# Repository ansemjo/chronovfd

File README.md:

# chronovfd

A vacuum-flourescent display (VFD) clock project based on Soviet NOS [IVL2-7/5 / ИВЛ2-7/5](https://www.ebay.com/sch/i.html?_nkw=ivl2-7%2F5) tubes. This has been my first somewhat complex hardware project when I got into electronics design in 2020 and grew to multiple iterations over the years.

#### quickmenu:

* [vfddriver](vfddriver/) — updated display board, which can be used over I2C
* [sandwich](sandwich/) — the original clock design with two boards
* [other](#other-directories) — links to initial research prototypes and various experiments

### vfddriver

This section describes the updated display board design, which I will be using going forward with this project. The [original design](#sandwich) of course still works but I found it needlessly complex later on due to a few choices I made.

Primarily, you needed to have a lot of IVL2-7/5 specific bits in the firmware and constantly refresh the display contents on the shift register. The mapping of display characters to segment anodes, their mapping to the correct shift-register pin, as well as the necessary anode and grid time-multiplexing all needed to be implemented on the controller board. Which meant that you really couldn't easily swap out the controller for something else. It had originally been a design goal not to require *any* separate firmware on the display board but I realized that just makes everything more complicated because you can't handle the display as an abstraction.

Instead, in this redesign I opted to include a small AVR ATtiny414 microcontroller, simplify the filament AC driver circuit with an H-bridge and implement the entire board as an I2C peripheral. **That newer design, along with firmware and documentation, can be found in [`vfddriver/`](vfddriver/).**

In these images above you can also see why there is no dedicated "clockdriver v2" yet: now that the VFD is controlled over I2C, you can just use a small CircuitPython board with a Qwiic cable, like the [Adafruit QT Py ESP32-S3](https://www.adafruit.com/product/5426). :)

### sandwich

What you see in the pictures below is the original "sandwich design" with a pure-logic display driver (more or less a wrapper around the HV5812 shift-register) and an ESP32-based design with an RTC and coin-cell backup for the controller board. You can find all the KiCAD files and firmware for it in [`sandwich/`](sandwich/), together with the original README and more photos.

### other directories

The **[research/](research/) directory** contains a lot of initial ideas and fundamental information on VFD operation (needed voltages etc.) along with the [display datasheets](research/ivl2-7_5-datasheets).

The first **prototype clock** on perfboard can be found in [research/protoclock/](research/protoclock/).

An alternative **LCD-based front panel** with compatible dimensions, which can also be used standalone in [lcddriver](lcddriver/).

In [experiments/si4706_radio_eval](experiments/si4706_radio_eval/) there is an evaluation board based on the **Skyworks Si4706 FM receiver** with RDS decoding. The idea is that you should be able to get time signal from radio stations without any need for internet synchronization.

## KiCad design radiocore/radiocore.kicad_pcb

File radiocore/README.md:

# radiocore
This is a redesign of the [`si4706_radio_eval`](../experiments/si4706_radio_eval/) experiment, meant to be a "clockcore v2" to control the standalone vfddriver.

Notably, it includes:

* **Skyworks Si4706** FM radio receiver with RDS decoder, to get time signal "from the air"
* **DS1338 RTC** with coin cell battery backup, to keep accurate time over long periods and without power
* **ESP32-C3** as a simple-to-program-over-USB controller chip, which conveniently *also* includes WiFi capability, if you prefer NTP over RDS
* vertical **GCT USB4145** USB-C connector, so a final assembly with two sandwiched boards will have the cable coming in from the back

_**2026-02-03:** I ordered the boards and am waiting to try if the CircuitPython firmware from the experiment will work on this chip as well. (**edit:** yes, it does!)_

### errata

While the overall function works (reception is even better than expected, to be honest), I also made a few major mistakes:

* The Neopixel is supplied with VBUS (~ 5V) but only gets logic level 3.3V on its data pin from the ESP32. When the VBUS supply voltage is slightly over 5V (like 5.2–5.3V), the Neopixel consistenly stays dark. When it is exactly at or slightly under 5V, you can *sometimes* get it to work. At 5V, the SK6812 requires a 3.6V logic level per the datasheet. Oops.

* The UPDI connection (pin 5 on the side header) is connected directly to the ESP32 without level shifting or current limit. Since this pin is at 5V logic level on the ATtiny, you could damage the ESP32-C3 if it is ever connected during programming of the `vfddriver`. Use a Qwiic cable only or just solder the first four pins to be safe.

* While it works out, the cutout under the Qwiic connector is a little close to properly insert the plug while the cable is already weaved through the hole.

* In the previous `vfddriver` firmware, the display's address was `0x68` and thus collided with the RTC. I've moved the VFD to address `0x42` and you can still reconfigure it using the `user_row`, of course.

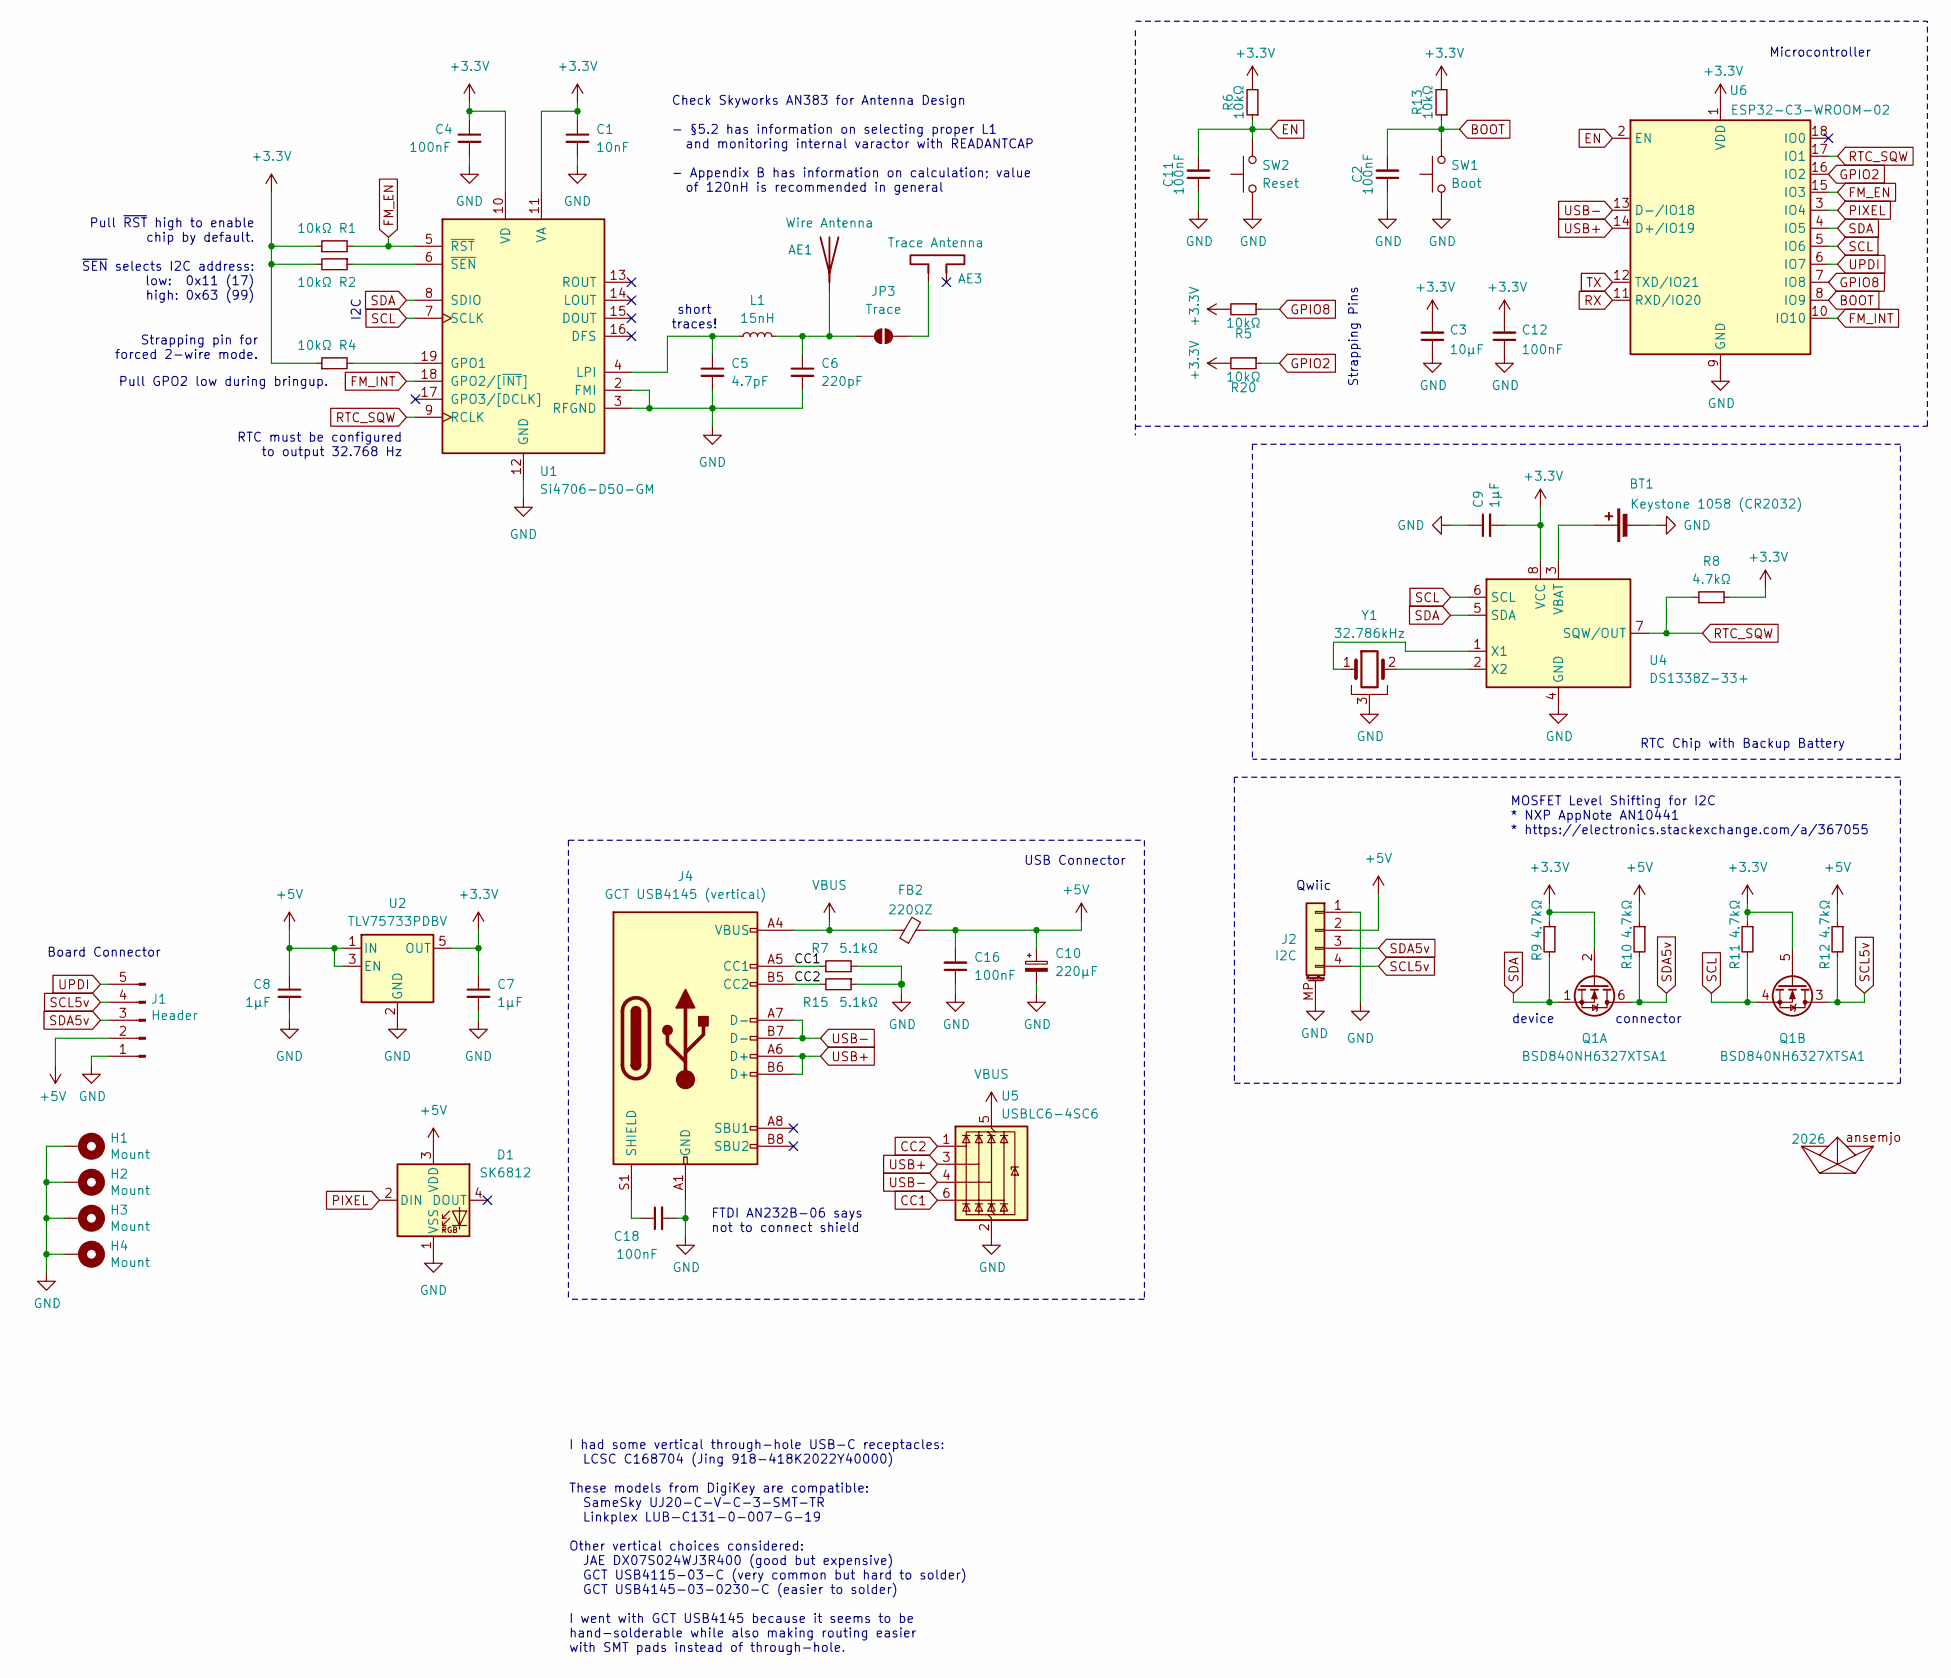
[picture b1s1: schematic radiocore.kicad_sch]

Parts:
A1: 2026; ahoi
AE1: Wire Antenna; TestPoint_THTPad_D2.0mm_Drill1.0mm
AE3: Trace Antenna
BT1: Keystone 1058 (CR2032); BatteryHolder_Keystone_1058_1x2032; MPN 1058; Digi-Key_PN 36-1058-ND
C1: 10nF; C_0805_2012Metric_Pad1.18x1.45mm_HandSolder
C2, C4, C11, C12, C16: 100nF; C_0805_2012Metric_Pad1.18x1.45mm_HandSolder
C3: 10µF; C_0805_2012Metric_Pad1.18x1.45mm_HandSolder
C5: 4.7pF; C_0805_2012Metric_Pad1.18x1.45mm_HandSolder
C6: 220pF; C_0805_2012Metric_Pad1.18x1.45mm_HandSolder
C7, C8: 1µF; C_0805_2012Metric_Pad1.18x1.45mm_HandSolder
C9: 1µF; C_0805_2012Metric_Pad1.18x1.45mm_HandSolder; MPN CL21B105KAFNNNG; Digi-Key_PN 1276-6469-1-ND
C10: 220µF; CP_EIA-3528-12_Kemet-T_HandSolder
C18: 100nF; C_0805_2012Metric_Pad1.18x1.45mm_HandSolder; MPN CL21B104KACNNNC; Digi-Key_PN 1276-1099-1-ND
D1: SK6812; LED_SK6812_PLCC4_5.0x5.0mm_P3.2mm
FB2: 220ΩZ; L_0805_2012Metric_Pad1.05x1.20mm_HandSolder
H1, H2, H3, H4: Mount; MountingHole_2.7mm_M2.5_Pad
J1: Header; PinHeader_1x05_P2.54mm_Vertical; MPN PREC040DBAN-M71RC; Digi-Key PN S2112EC-40-ND
J2: I2C; JST_SH_SM04B-SRSS-TB_1x04-1MP_P1.00mm_Horizontal
J4: GCT USB4145 (vertical); GCT_USB4145-03-0230-C_REVA2
JP3: Trace; SolderJumper-2_P1.3mm_Open_RoundedPad1.0x1.5mm
L1: 15nH; L_0805_2012Metric_Pad1.05x1.20mm_HandSolder
Q1: BSD840NH6327XTSA1; SOT-363_SC-70-6
R1, R2, R4, R5, R6, R13, R20: 10kΩ; R_0805_2012Metric_Pad1.20x1.40mm_HandSolder
R7, R15: 5.1kΩ; R_0805_2012Metric_Pad1.20x1.40mm_HandSolder
R8: 4.7kΩ; R_0805_2012Metric_Pad1.20x1.40mm_HandSolder; MPN RC0805FR-074K7L; Digi-Key_PN 311-4.70KCRCT-ND
R9, R10, R11, R12: 4.7kΩ; R_0805_2012Metric_Pad1.20x1.40mm_HandSolder
SW1: Boot; SW_SPST_PTS810
SW2: Reset; SW_SPST_PTS810
U1: Si4706-D50-GM; SiliconLabs_QFN-20-1EP_3x3mm_P0.5mm_EP1.8x1.8mm
U2: TLV75733PDBV; SOT-23-5
U4: DS1338Z-33+; SOIC-8_3.9x4.9mm_P1.27mm; MPN DS1338Z-33+T&R; Digi-Key_PN DS1338Z-33+T&RCT-ND
U5: USBLC6-4SC6; SOT-23-6; MPN USBLC6-4SC6; Digi-Key_PN 497-4492-1-ND
U6: ESP32-C3-WROOM-02; ESP-WROOM-02
Y1: 32.786kHz; Crystal_SMD_MicroCrystal_MS1V-T1K

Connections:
+3.3V: C1.1, C3.2, C4.1, C7.1, C9.2, C12.2, Q1.2 (G), Q1.5 (G), R1.1, R2.2, R4.1, R5.2, R6.2, R8.2, R9.1, R11.1, R13.2, R20.2, U1.10 (VD), U1.11 (VA), U2.5 (OUT), U4.8 (VCC), U6.1 (VDD)
+5V: C8.1, C10.1, C16.2, D1.3 (VDD), FB2.2, J1.2, J2.2, R10.1, R12.1, U2.1 (IN), U2.3 (EN)
BOOT: C2.2, R13.1, SW1.2, U6.8 (IO9)
CC1: J4.A5 (CC1), R7.1, U5.6 (I/O4)
CC2: J4.B5 (CC2), R15.2, U5.1 (I/O1)
EN: C11.2, R6.1, SW2.2, U6.2 (EN)
FM_EN: R1.2, U1.5 (~RST), U6.15 (IO3)
FM_INT: U1.18 (GPO2/[~INT]), U6.10 (IO10)
GND: BT1.2 (-), C1.2, C2.1, C3.1, C4.2, C5.2, C6.2, C7.2, C8.2, C9.1, C10.2, C11.1, C12.1, C16.1, C18.2, D1.1 (VSS), H1.1, H2.1, H3.1, H4.1, J1.1, J2.1, J2.MP (MountPin), J4.A1 (GND), J4.A12 (GND), J4.B1 (GND), J4.B12 (GND), R7.2, R15.1, SW1.1, SW2.1, U1.2 (FMI), U1.3 (RFGND), U1.12 (GND), U1.21 (GND), U2.2 (GND), U4.4 (GND), U5.2 (GND), U6.9 (GND), U6.19 (GND), Y1.3
GPIO2: R20.1, U6.16 (IO2)
GPIO8: R5.1, U6.7 (IO8)
unnamed: AE1.1 (A), C6.1, JP3.1 (A), L1.2
unnamed: BT1.1 (+), U4.3 (VBAT)
unnamed: C18.1, J4.S1 (SHIELD)
unnamed: AE3.1, JP3.2 (B)
unnamed: R4.2, U1.19 (GPO1)
unnamed: C5.1, L1.1, U1.4 (LPI)
unnamed: R2.1, U1.6 (~SEN)
unnamed: U4.1 (X1), Y1.1
unnamed: U4.2 (X2), Y1.2
PIXEL: D1.2 (DIN), U6.3 (IO4)
RTC_SQW: R8.1, U1.9 (RCLK), U4.7 (SQW/OUT), U6.17 (IO1)
RX: U6.11 (RXD/IO20)
SCL: Q1.4 (S), R11.2, U1.7 (SCLK), U4.6 (SCL), U6.5 (IO6)
SCL5v: J1.4, J2.4, Q1.3 (D), R12.2
SDA: Q1.1 (S), R9.2, U1.8 (SDIO), U4.5 (SDA), U6.4 (IO5)
SDA5v: J1.3, J2.3, Q1.6 (D), R10.2
TX: U6.12 (TXD/IO21)
UPDI: J1.5, U6.6 (IO7)
USB+: J4.A6 (D+), J4.B6 (D+), U5.3 (I/O2), U6.14 (D+/IO19)
USB-: J4.A7 (D-), J4.B7 (D-), U5.4 (I/O3), U6.13 (D-/IO18)
VBUS: FB2.1, J4.A4 (VBUS), J4.A9 (VBUS), J4.B4 (VBUS), J4.B9 (VBUS), U5.5 (VBUS)

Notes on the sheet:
USB Connector
Microcontroller
RTC Chip with Backup Battery
Qwiic
short traces!
Board Connector
RTC must be configured to output 32.768 Hz
I2C
Check Skyworks AN383 for Antenna Design - §5.2 has information on selecting proper L1 and monitoring internal varactor with READANTCAP - Appendix B has information on calculation; value of 120nH is recommended in general
device
FTDI AN232B-06 says not to connect shield
I had some vertical through-hole USB-C receptacles: LCSC C168704 (Jing 918-418K2022Y40000) These models from DigiKey are compatible: SameSky UJ20-C-V-C-3-SMT-TR Linkplex LUB-C131-0-007-G-19 Other vertical choices considered: JAE DX07S024WJ3R400 (good but expensive) GCT USB4115-03-C (very common but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
Pull ~{RST} high to enable chip by default. ~{SEN} selects I2C address: low: 0x11 (17) high: 0x63 (99)
connector
Pull GPO2 low during bringup.
Strapping Pins
MOSFET Level Shifting for I2C * NXP AppNote AN10441 * https://electronics.stackexchange.com/a/367055
Strapping pin for forced 2-wire mode.

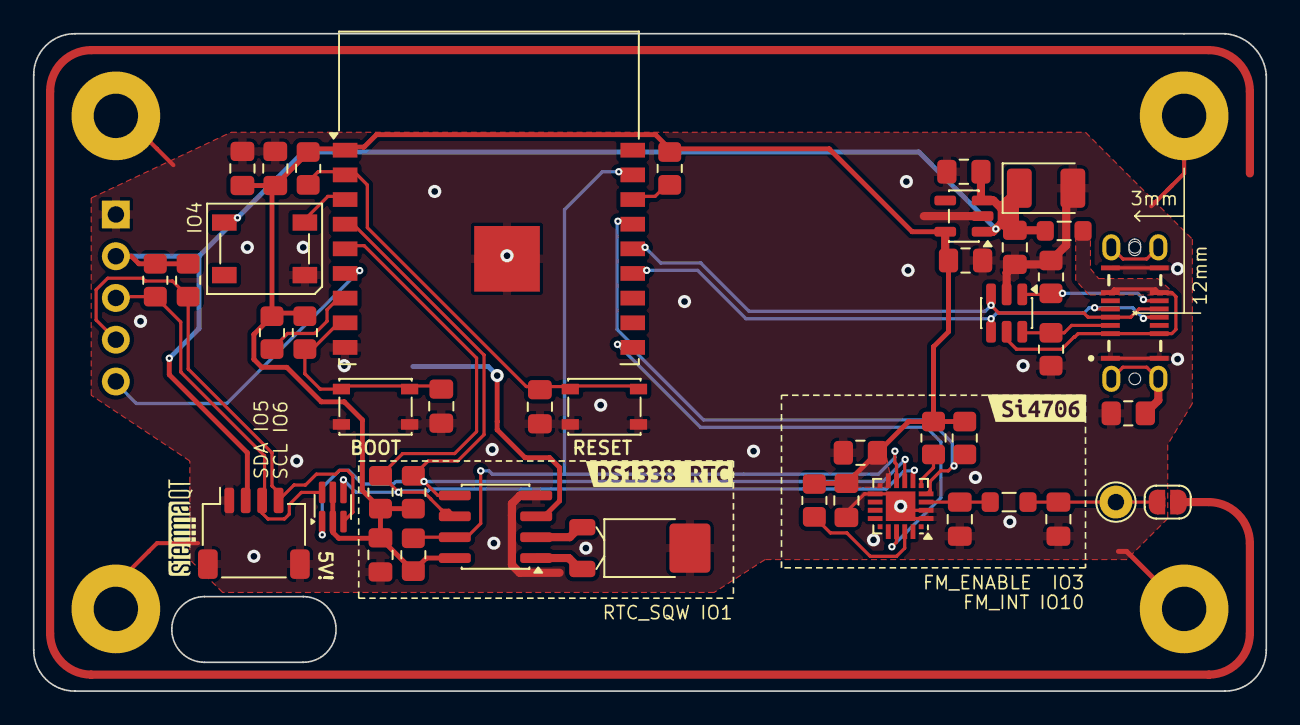
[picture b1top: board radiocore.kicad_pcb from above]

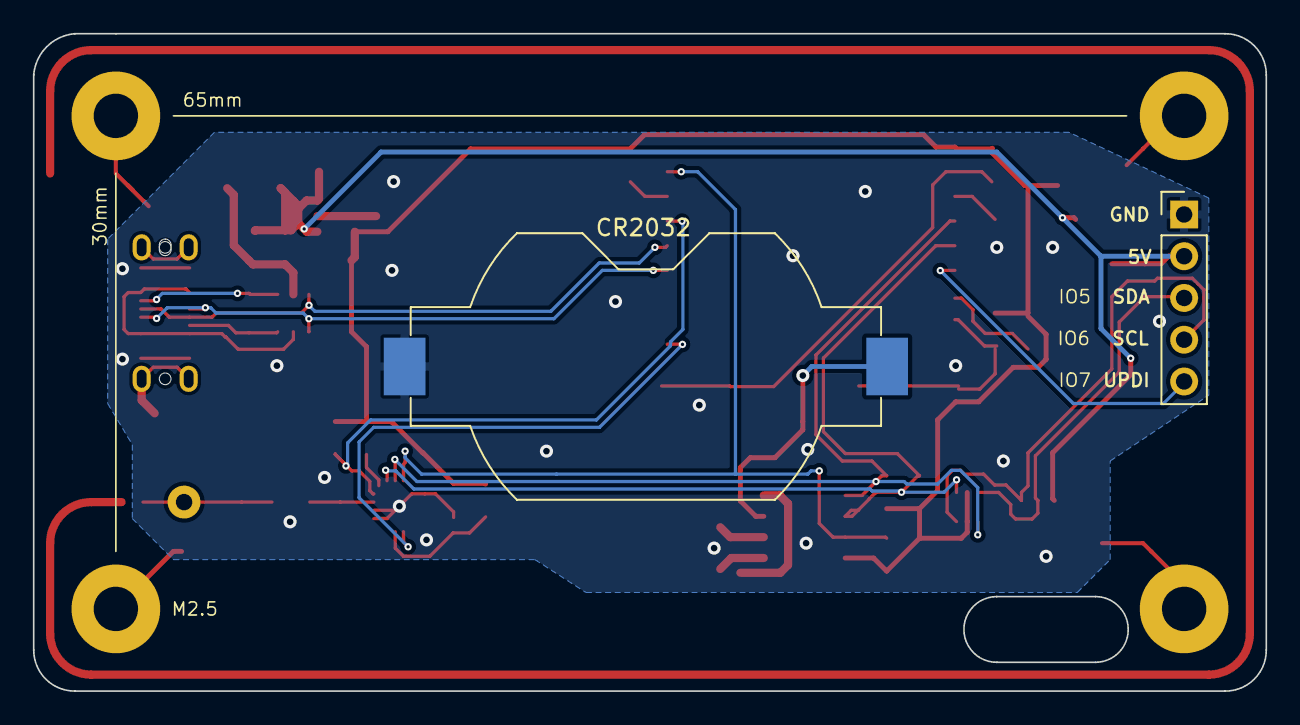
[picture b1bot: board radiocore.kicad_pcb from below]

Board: 2 copper layers, 75.0 x 40.0 mm, 54 parts (2 on the bottom side), 29 nets.

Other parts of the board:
kibuzzard-69810B1B: G***; kibuzzard-69810B1B
kibuzzard-69810B5E: G***; kibuzzard-69810B5E
kibuzzard-69811623: G***; kibuzzard-69811623

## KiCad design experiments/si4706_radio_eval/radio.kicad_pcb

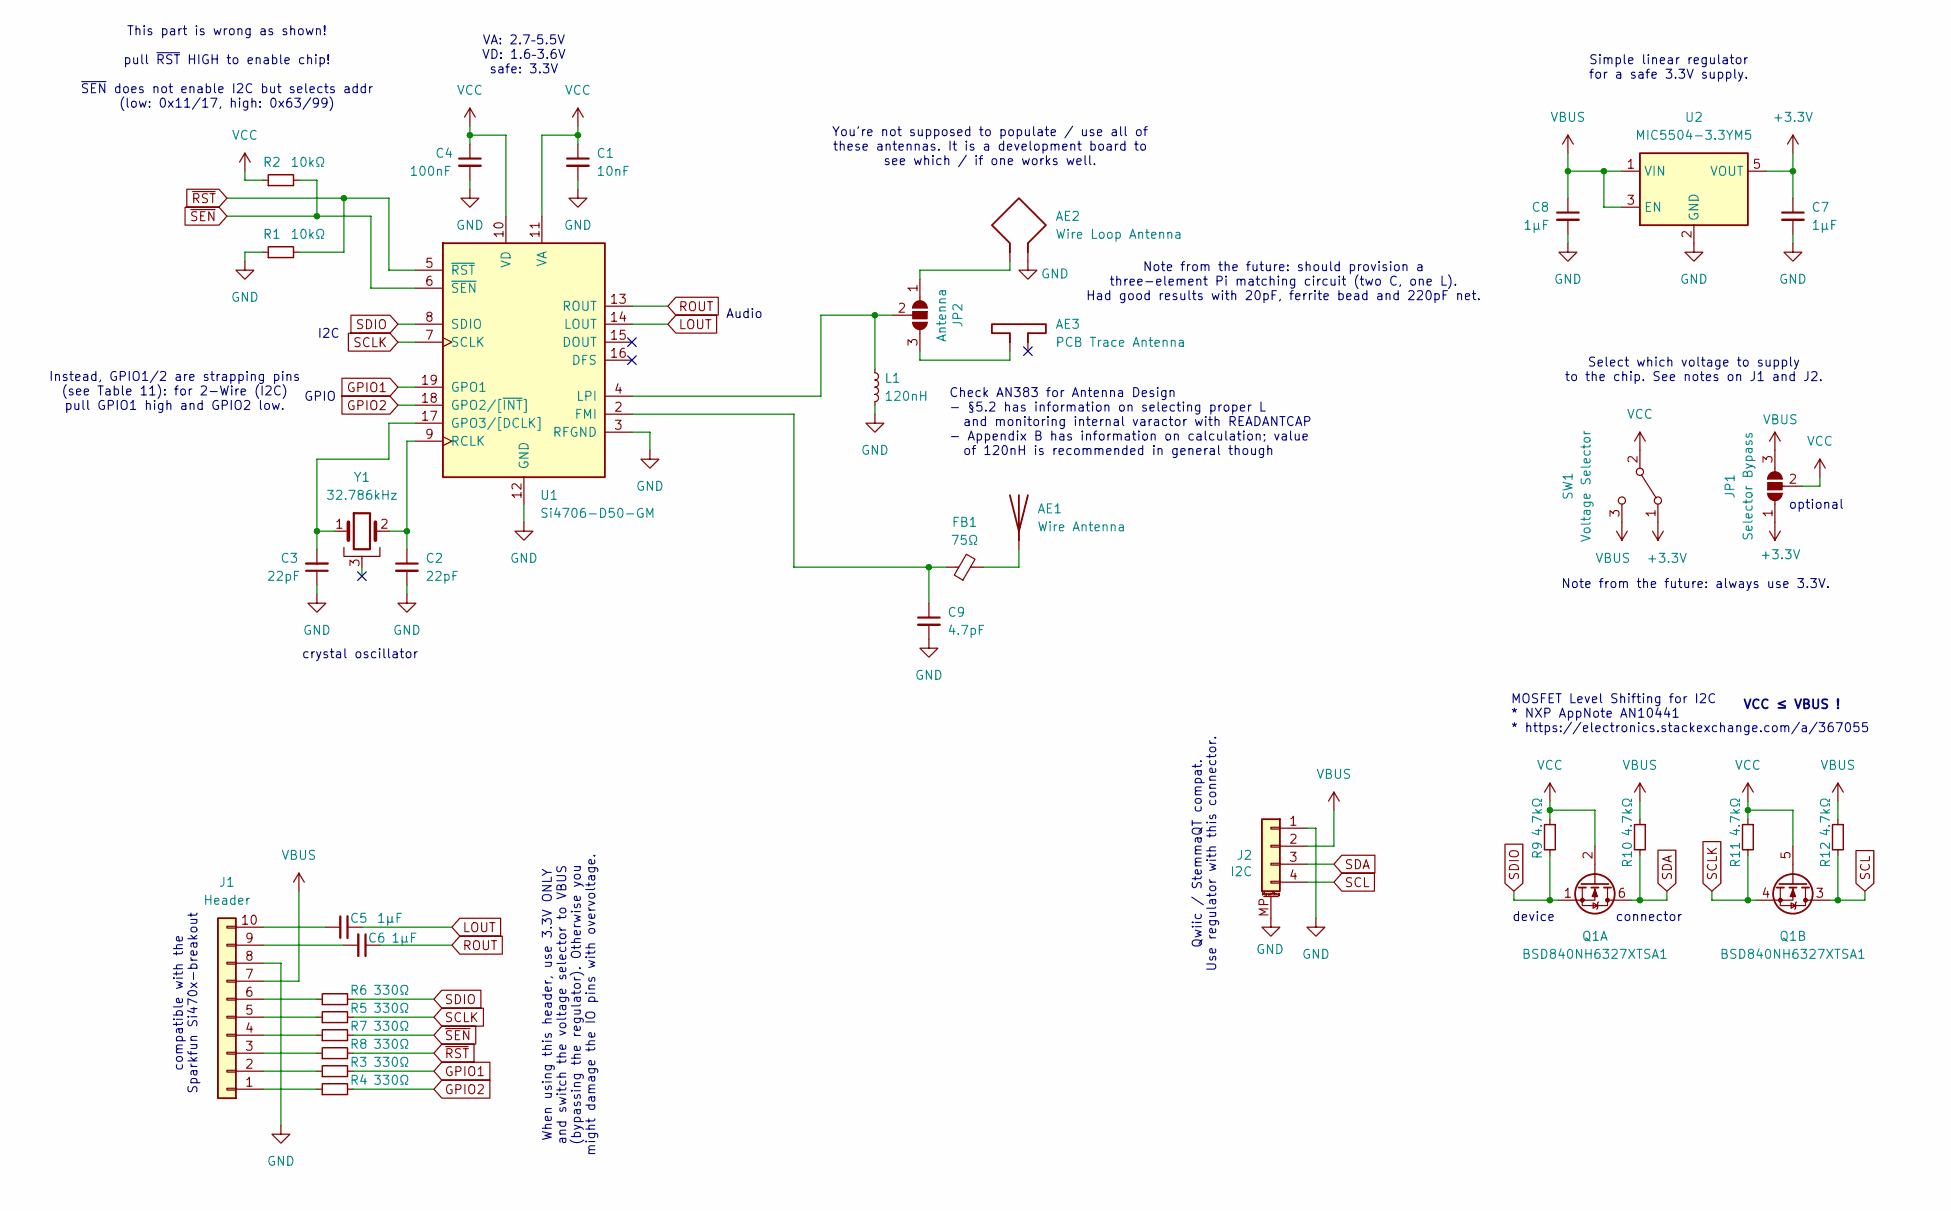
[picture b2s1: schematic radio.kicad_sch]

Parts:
AE1: Wire Antenna; TestPoint_Loop_D2.50mm_Drill1.0mm
AE2: Wire Loop Antenna; TestPoint_2Pads_Pitch2.54mm_Drill0.8mm
AE3: PCB Trace Antenna
C1: 10nF; C_0805_2012Metric
C2, C3: 22pF; C_0603_1608Metric
C4: 100nF; C_0805_2012Metric
C5, C6, C7, C8: 1µF; C_0805_2012Metric
C9: 4.7pF; C_0603_1608Metric
FB1: 75Ω; L_0603_1608Metric
J1: Header; PinHeader_1x10_P2.54mm_Vertical
J2: I2C; JST_SH_SM04B-SRSS-TB_1x04-1MP_P1.00mm_Horizontal
JP1: Selector Bypass; SolderJumper-3_P1.3mm_Open_RoundedPad1.0x1.5mm
JP2: Antenna; SolderJumper-3_P1.3mm_Open_RoundedPad1.0x1.5mm
L1: 120nH; L_0603_1608Metric
Q1: BSD840NH6327XTSA1; SOT-363_SC-70-6
R1, R2: 10kΩ; R_0805_2012Metric
R3, R4, R5, R6, R7, R8: 330Ω; R_0805_2012Metric
R9, R10, R11, R12: 4.7kΩ; R_0805_2012Metric
SW1: Voltage Selector; SW_SPDT_PCM12
U1: Si4706-D50-GM; SiliconLabs_QFN-20-1EP_3x3mm_P0.5mm_EP1.8x1.8mm
U2: MIC5504-3.3YM5; SOT-23-5
Y1: 32.786kHz; Crystal_SMD_MicroCrystal_MS1V-T1K

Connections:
+3.3V: C7.1, JP1.1 (A), SW1.1 (A), U2.5 (VOUT)
GND: AE2.2, C1.2, C2.2, C3.1, C4.2, C7.2, C8.2, C9.2, J1.8, J2.1, J2.MP (MountPin), L1.2, R1.1, U1.3 (RFGND), U1.12 (GND), U1.21 (GND), U2.2 (GND)
GPIO1: R3.2, U1.19 (GPO1)
GPIO2: R4.2, U1.18 (GPO2/[~INT])
LOUT: C5.2, U1.14 (LOUT)
unnamed: AE1.1 (A), FB1.2
unnamed: J1.1, R4.1
unnamed: J1.2, R3.1
unnamed: J1.3, R8.1
unnamed: J1.4, R7.1
unnamed: J1.5, R5.1
unnamed: J1.6, R6.1
unnamed: C6.2, J1.9
unnamed: C5.1, J1.10
unnamed: AE2.1, JP2.1 (A)
unnamed: AE3.1, JP2.3 (B)
unnamed: JP2.2 (C), L1.1, U1.4 (LPI)
unnamed: C9.1, FB1.1, U1.2 (FMI)
unnamed: C3.2, U1.17 (GPO3/[DCLK]), Y1.1
unnamed: C2.1, U1.9 (RCLK), Y1.2
ROUT: C6.1, U1.13 (ROUT)
SCL: J2.4, Q1.3 (D), R12.2
SCLK: Q1.4 (S), R5.2, R11.2, U1.7 (SCLK)
SDA: J2.3, Q1.6 (D), R10.2
SDIO: Q1.1 (S), R6.2, R9.2, U1.8 (SDIO)
VBUS: C8.1, J1.7, J2.2, JP1.3 (B), R10.1, R12.1, SW1.3 (C), U2.1 (VIN), U2.3 (EN)
VCC: C1.1, C4.1, JP1.2 (C), Q1.2 (G), Q1.5 (G), R2.1, R9.1, R11.1, SW1.2 (B), U1.10 (VD), U1.11 (VA)
~RST: R1.2, R8.2, U1.5 (~RST)
~SEN: R2.2, R7.2, U1.6 (~SEN)

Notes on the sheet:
Note from the future: always use 3.3V.
Simple linear regulator for a safe 3.3V supply.
crystal oscillator
Qwiic / StemmaQT compat. Use regulator with this connector.
compatible with the Sparkfun Si470x-breakout
Audio
You're not supposed to populate / use all of these antennas. It is a development board to see which / if one works well.
I2C
Select which voltage to supply to the chip. See notes on J1 and J2.
Check AN383 for Antenna Design - §5.2 has information on selecting proper L and monitoring internal varactor with READANTCAP - Appendix B has information on calculation; value of 120nH is recommended in general though
Note from the future: should provision a three-element Pi matching circuit (two C, one L). Had good results with 20pF, ferrite bead and 220pF net.
device
When using this header, use 3.3V ONLY and switch the voltage selector to VBUS (bypassing the regulator). Otherwise you might damage the IO pins with overvoltage.
This part is wrong as shown! pull ~{RST} HIGH to enable chip! ~{SEN} does not enable I2C but selects addr (low: 0x11/17, high: 0x63/99)
connector
VA: 2.7–5.5V VD: 1.6–3.6V safe: 3.3V
optional
GPIO
MOSFET Level Shifting for I2C * NXP AppNote AN10441 * https://electronics.stackexchange.com/a/367055
VCC ≤ VBUS !
Instead, GPIO1/2 are strapping pins (see Table 11): for 2-Wire (I2C) pull GPIO1 high and GPIO2 low.

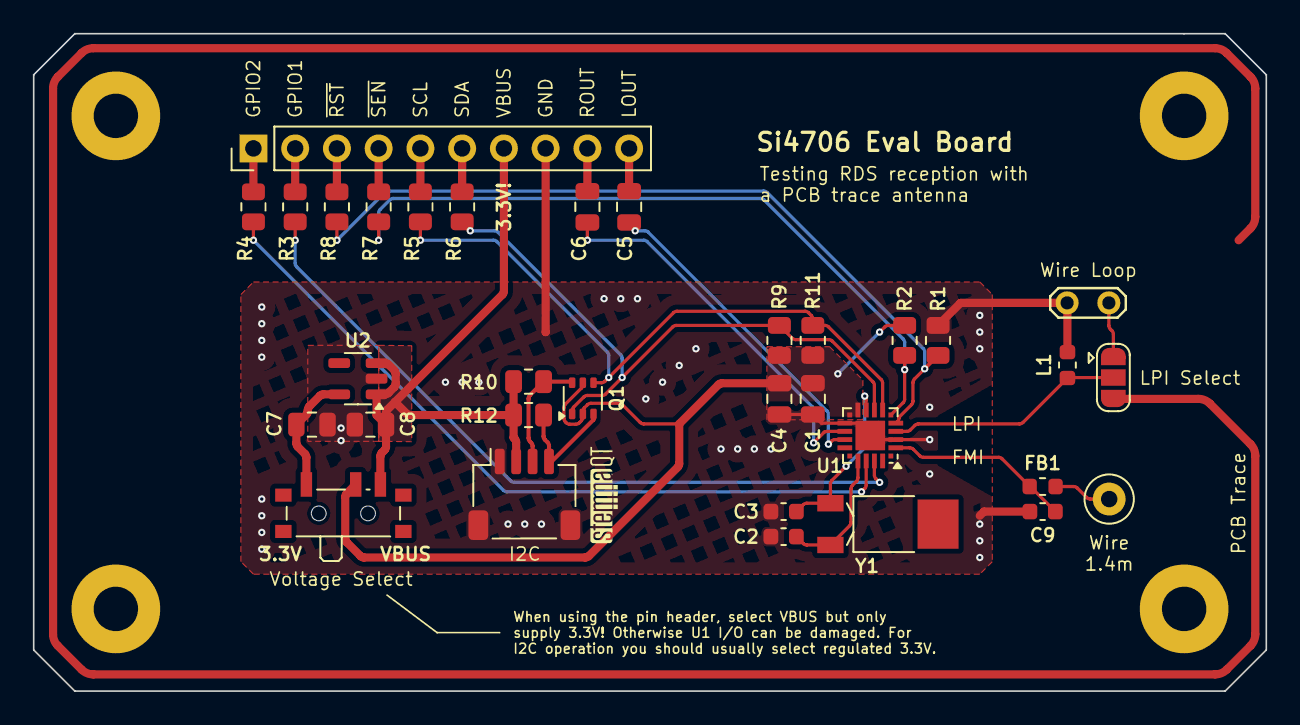
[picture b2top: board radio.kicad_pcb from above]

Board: 2 copper layers, 75.0 x 40.0 mm, 33 parts (0 on the bottom side), 28 nets.

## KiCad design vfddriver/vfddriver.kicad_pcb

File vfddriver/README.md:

# vfddriver (v2)

A standalone driver board for four-digit IVL2-7/5 vacuum-flourescent display (VFD) tubes.

view: [schematic](https://kicanvas.org/?repo=https%3A%2F%2Fgithub.com%2Fansemjo%2Fchronovfd%2Fblob%2Fmain%2Fvfddriver%2Fvfddriver.kicad_sch) –
[circuit board](https://kicanvas.org/?repo=https%3A%2F%2Fgithub.com%2Fansemjo%2Fchronovfd%2Fblob%2Fmain%2Fvfddriver%2Fvfddriver.kicad_pcb) –
[firmware](firmware/) –
[parts list](https://www.digikey.de/de/mylists/list/2BJCAMLMTA) –
[ibom](https://htmlpreview.github.io/?https://github.com/ansemjo/chronovfd/blob/main/vfddriver/ibom.html)

## hardware

You can find a lot of fundamental information on VFD operating principles in [this excellent Noritake guide](https://www.noritake-elec.com/technology/general-technical-information/vfd-operation) ([archive](https://archive.is/BsdLR)). As a very brief overview, the filament is emitting electrons from a constant current, which are accelerated towards the positive grids over each segment and when the electrons hit a phosphor-coated segment, it starts glowing brightly.

* High-voltage (24V) for the grids and anodes is supplied using a simple [TI LM2733YMF](https://www.ti.com/lit/gpn/lm2733) boost converter.
* A [Microchip HV5812](https://ww1.microchip.com/downloads/aemDocuments/documents/OTH/ProductDocuments/DataSheets/20005629A.pdf) shift register with high-voltage MOSFET outputs is used to supply the grids and anodes with 24V, while being safe to use with 5V logic.
* The filament requires alternating current for best luminous uniformity. This is provided by a [Diodes Inc. ZXBM5210](https://www.diodes.com/datasheet/download/ZXBM5210.pdf) (or equivalently, [Rohm BD6211F](https://fscdn.rohm.com/en/products/databook/datasheet/ic/motor/dc/bd621x-e.pdf)) H-bridge motor driver by toggling the FWD/REV direction pins and using Vref to adjust the effective RMS voltage, which directly influences the overall brightness.
* Everything is controlled using an [AVR ATtiny414 microcontroller](https://www.microchip.com/en-us/product/attiny414), which acts as a peripheral on an I2C bus. Since the segments on all digits are connected, it needs to use time-multiplexing over the grids and constantly refresh the shift-register sufficiently quickly for a smooth appearance. The AVR also translates received ASCII characters to the actual segment anodes.

So far, I have ordered the PCBs from [AISLER.net](https://aisler.net/), who produce locally (to me) using the pretty gold ENIG finish and accept KiCAD files directly. Parts were [ordered from DigiKey](https://www.digikey.de/de/mylists/list/2BJCAMLMTA) and assembly was done by hand using the [interactive BOM viewer](https://htmlpreview.github.io/?https://github.com/ansemjo/chronovfd/blob/main/vfddriver/ibom.html).

### segments

In the render above, you can see the HV5812 pin numbering and mapping to grids (`G1`, `G2`, `Gc`, `G3`, `G4`) and segments (`a`–`g`, `db`, `dt`), with pin 1 being the "latest" shifted bit:

|anode|G4|a|f|b|G3|d|db|Gc|c|G2|e|g|dt|G1|
|-|-|-|-|-|-|-|-|-|-|-|-|-|-|-|
|**pin**|10|9|8|7|6|5|4|3|2|1|11|12|13|14|

For convenience, here is the same table in terms of bits in a `u16`:

|anode|G1|dt|g|e|G4|a|f|b|G3|d|db|Gc|c|G2
|-|-|-|-|-|-|-|-|-|-|-|-|-|-|-|
|**bit**|13|12|11|10|9|8|7|6|5|4|3|2|1|0|

The segments in a digit are counted clockwise, starting from the top; the center dash is last and the two dots in the colon can be adressed individually as well:

```
      a            a                a            a     
    ────         ────             ────         ────    
 f │    │     f │    │     dt  f │    │     f │    │   
   │  g │ b     │  g │ b   ■     │  g │ b     │  g │ b 
    ────         ────             ────         ────    
 e │    │     e │    │     db  e │    │     e │    │   
   │  d │ c     │  d │ c   ■     │  d │ c     │  d │ c 
    ────         ────             ────         ────    
                                                        
     G1           G2       Gc       G3           G4     
```

## firmware

The firmware was ported to Rust using the [`avr-none`](https://doc.rust-lang.org/stable/rustc/platform-support/avr-none.html) target and [`rahix/avr-device`](https://github.com/Rahix/avr-device) crate. Even though this is effectively still register-fiddling, since there currently is no proper HAL for ATtiny 0/1-series chips, the development experience was much more pleasant already.
*(Note: the previous C firmware can be found in [commit `2b87ed3`](https://github.com/ansemjo/chronovfd/tree/2b87ed39b4a0b78c596b9a6d270321534c5b3cb9/vfddriver/firmware), though it has fallen behind feature-wise.)*

### building

I am not exactly sure what the absolute minimum required version is for a successful build. But I can say that the firmware easily builds in a current `rust:trixie` container.

You should be able to just run `cargo build` after installing `gcc-avr` and `avr-libc`. The resulting `firmware.elf` then just needs to be converted to a HEX file using `avr-objcopy` before flashing.

```
$ docker run --rm -it -v firmware/:/firmware -w /firmware rust:latest

# apt update && apt install -y gcc-avr avr-libc
// binutils-avr amd64 2.43.50.20250108-1
// gcc-avr amd64 1:14.2.0-2
// avr-libc all 1:2.2.1-1

# cargo build
info: syncing channel updates for 'nightly-x86_64-unknown-linux-gnu'
info: latest update on 2026-01-31, rust version 1.95.0-nightly (a293cc4af 2026-01-30)
// ...
    Finished `dev` profile [optimized + debuginfo] target(s) in 26.26s

# avr-objcopy -O ihex -R .eeprom target/avr-none/debug/firmware.{elf,hex}
# avr-size target/avr-none/debug/firmware.hex
   text	   data	    bss	    dec	    hex	filename
      0	   3658	      0	   3658	    e4a	firmware.hex
```

A compiled firmware is also committed in this repository, though I won't guarantee that I will always keep it updated with every commit. (:

### flashing

The ATtiny 0/1/2-series chips can be flashed using an UPDI programmer, which can be as simple as connecting a Schottky diode or resistor between the RX and TX pins of a USB-TTL adapter: [SpenceKonde/AVR-Guidance/UPDI/jtag2updi.md](https://github.com/SpenceKonde/AVR-Guidance/blob/master/UPDI/jtag2updi.md#connections). I have my own programmer based on a CH340N chip, very similar to [this pogo pin adapter](https://oshwlab.com/gabe_9484/usb-c-to-updi).

Using serial adapters like this, you can then use [`pymcuprog`](https://pypi.org/project/pymcuprog/) to flash the firmware:

```
pymcuprog -d attiny414 -t uart -u /dev/ttyUSB0 write \
 --erase -f firmware/target/avr-none/debug/firmware.hex
```

### configuration

For persistent configuration, you can write values to the ATtiny414's USERROW — a special region in the EEPROM (`0x1300`), which is not deleted when flashing new firmware. You can again use `pymcuprog` to set these values. Erasing the region or writing a `0xff` always means "use hardcoded defaults", since this is the default when you haven't modified the USERROW.

```
pymcuprog -d attiny414 -t uart -u /dev/ttyUSB0 write \
 -m user_row -o 0x01 -l 160 # default brightness
```

| Offset | Type | Default | Description |
| ------ | ---- | --------| ----------- |
| `0x00` | `u8` | `0x42` | I2C peripheral address |
| `0x01` | `u8` | 120 | filament brightness (DAC value) |
| `0x02` | `u16` | 10.000 | digit multiplexing frequency in Hz |
| `0x0b` | `[u8; 5]` | `0xff..ff` | initial display contents |
| `0x10` | `[u8; 16]` | `[0, 1, 2, 3, 4]` | grid multiplex loop |

The grid multiplex loop can be used to adjust the relative brightness of grids, if they do not light up evenly. For example, if your first and last digits are darker at the edges, write:

```
pymcuprog -d attiny414 -t uart -u /dev/ttyUSB0 write \
 -m user_row -o 0x10 -l 0 0 1 2 3 4 4 0xff
```

## usage

The default I2C address of the display is `0x42`. Since the primary usage will be writing new display contents, the firmware will try to parse *most* bytes as bare numbers, ASCII characters or raw segment bitmaps. There are only two special command sequences which change the behaviour with the first transmitted byte; otherwise the display always expects exactly five bytes for the new display contents, from left to right, with the colon in the middle.

```
# HE LO
i2c.writeto(0x42, "HE LO")
```

#### commands

The two commands currently are:

* `[ 0x10, <u8> ]`: adjust display brightness with a new filament DAC value
* `[ 0x7f ]` (ASCII `DEL`): clear display (all segments off)

Future additions will probably use the non-printable range after `0x10`.

#### bare numbers

The byte values `0x00` to `0x09` are simply interpreted as decimal numbers.

So `[ 0x01, 0x02, 0x00, 0x03, 0x04 ]` would display `12 34`.

#### segment bitmap

The non-printable range above `0x80` is treated as raw bitmaps to the segments. To make it easier to think about, the bits are mapped from "left to right" (MSB to LSB) in the same clockwise order as they are named `a` to `g`: `0b1abcdefg` (bits `b` and `c` additionally map to `dt` and `db`).

Showing the "identical to" symbol `≡` with three horizontal bars could therefore be done by transmitting:

```
  1abcdefg
0b11001001
```

#### characters

All the remaining bytes are mapped from the ASCII characters, where possible. Since the digits are only sevent-segments digits, you can't really display the full alphabet well; for the colon only `:`, `.` and ` ` are really useful, etc. But this also allows you to simply format a `HH:MM` string with the time on your controller and transmit that as bytes.

#### examples

A few more examples that you might use from CircuitPython:

```
# 23:59
i2c.writeto(0x42, "23:59")
i2c.writeto(0x42, bytes([2, 3, 0xff, 5, 9]))
# 20°C
i2c.writeto(0x42, "20 *C")
```

```
# An.on                    A     n        .        o     n
i2c.writeto(0x42, bytes([0x41, 0x6e, 0b10010000, 0x6f, 0x6e]))
```

```
# lower brigthness
i2c.writeto(0x42, bytes([0x10, 65]))
```

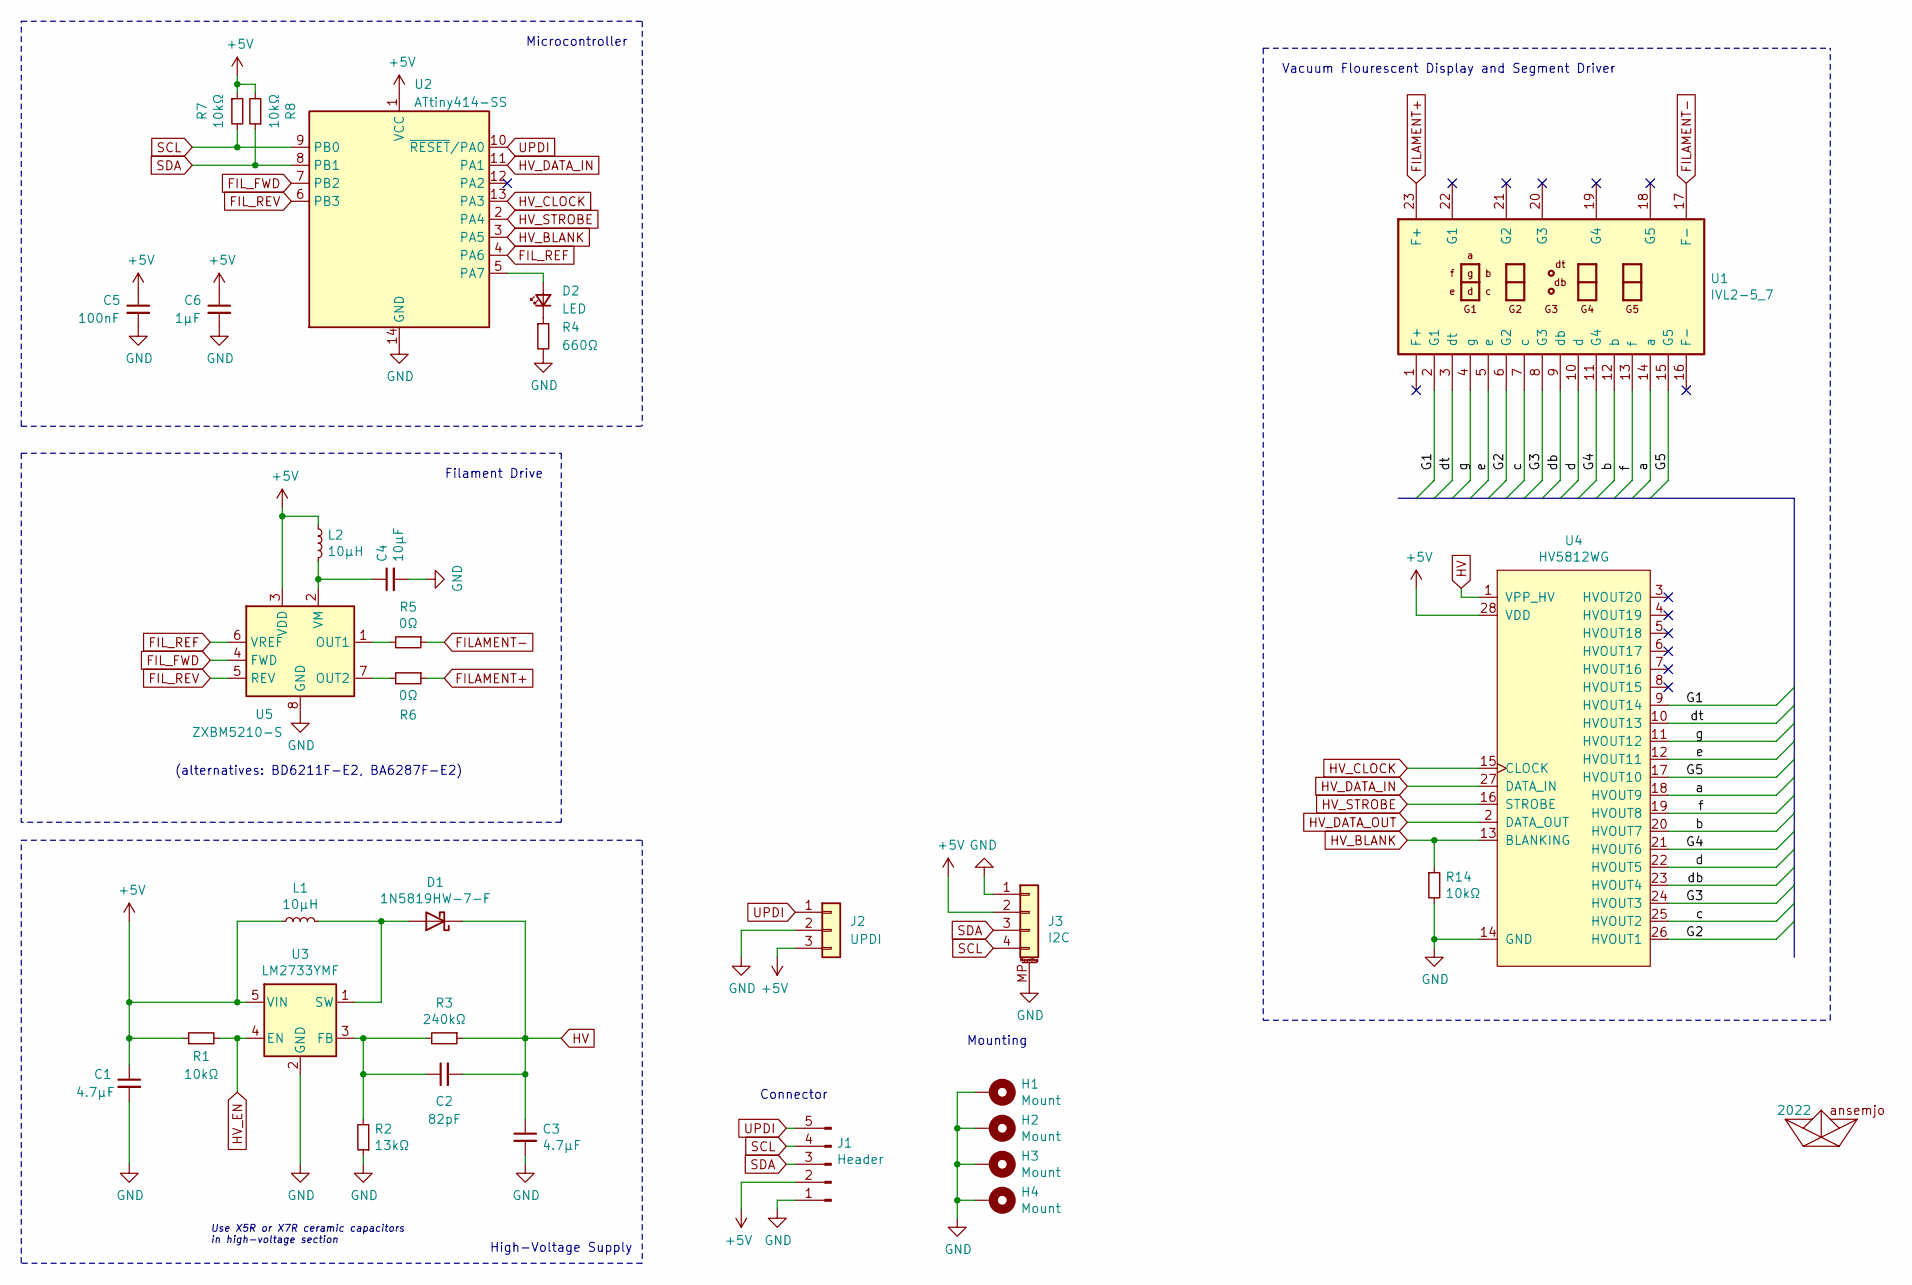
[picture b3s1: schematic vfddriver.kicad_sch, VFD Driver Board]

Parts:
A1: 2022; ahoi-mask
C1, C3: 4.7µF; C_0805_2012Metric_Pad1.18x1.45mm_HandSolder; MPN UMK212BBJ475KG-T; Digi-Key PN 587-5485-1-ND
C2: 82pF; C_0805_2012Metric_Pad1.18x1.45mm_HandSolder; MPN CC0805JRNPO9BN820; Digi-Key PN 311-1110-1-ND
C4: 10µF; C_0805_2012Metric_Pad1.18x1.45mm_HandSolder
C5: 100nF; C_0805_2012Metric_Pad1.18x1.45mm_HandSolder; MPN UMK212BBJ475KG-T; Digi-Key PN 587-5485-1-ND
C6: 1µF; C_0805_2012Metric_Pad1.18x1.45mm_HandSolder; MPN UMK212BBJ475KG-T; Digi-Key PN 587-5485-1-ND
D1: 1N5819HW-7-F; D_SOD-123; MPN 1N5819HW-7-F; Digi-Key PN 1N5819HW-FDICT-ND
D2: LED; LED_0805_2012Metric_Pad1.15x1.40mm_HandSolder
H1, H2, H3, H4: Mount; MountingHole_2.7mm_M2.5_Pad
J1: Header; PinHeader_1x05_P2.54mm_Vertical; MPN PREC040DBAN-M71RC; Digi-Key PN S2112EC-40-ND
J2: UPDI; UPDI_PogoProg_pinHoles
J3: I2C; JST_SH_SM04B-SRSS-TB_1x04-1MP_P1.00mm_Horizontal
L1: 10µH; L_1210_3225Metric_Pad1.42x2.65mm_HandSolder; MPN LBC3225T100MR; Digi-Key PN 587-6332-1-ND
L2: 10µH; L_1210_3225Metric_Pad1.42x2.65mm_HandSolder
R1, R14: 10kΩ; R_0805_2012Metric_Pad1.20x1.40mm_HandSolder; MPN RC0805FR-0747KL; Digi-Key PN 311-47.0KCRCT-ND
R2: 13kΩ; R_0805_2012Metric_Pad1.20x1.40mm_HandSolder; MPN RC0805FR-0713KL; Digi-Key PN 311-13.0KCRCT-ND
R3: 240kΩ; R_0805_2012Metric_Pad1.20x1.40mm_HandSolder; MPN RC0805FR-07240KL; Digi-Key PN 311-240KCRCT-ND
R4: 660Ω; R_0805_2012Metric_Pad1.20x1.40mm_HandSolder
R5, R6: 0Ω; R_1206_3216Metric_Pad1.30x1.75mm_HandSolder
R7, R8: 10kΩ; R_0805_2012Metric_Pad1.20x1.40mm_HandSolder; MPN RC0805FR-0710KL; Digi-Key PN 311-10.0KCRCT-ND
U1: IVL2-5_7; IVL2-7_5; MPN IVL2-7/5
U2: ATtiny414-SS; SOIC-14_3.9x8.7mm_P1.27mm
U3: LM2733YMF; SOT-23-5_HandSoldering; MPN LM2733YMF/NOPB; Digi-Key PN LM2733YMF/NOPBCT-ND
U4: HV5812WG; SOIC-28W_7.5x17.9mm_P1.27mm; MPN HV5812WG-G; Digi-Key PN HV5812WG-GCT-ND
U5: ZXBM5210-S; SOIC-8_3.9x4.9mm_P1.27mm

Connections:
+5V: C1.1, C5.1, C6.1, J1.2, J2.3, J3.2, L1.1, L2.1, R1.1, R7.1, R8.2, U2.1 (VCC), U3.5 (VIN), U4.28 (VDD), U5.3 (VDD)
/G1: U1.2 (G1), U4.9 (HVOUT14)
/G2: U1.6 (G2), U4.26 (HVOUT1)
/G3: U1.8 (G3), U4.24 (HVOUT3)
/G4: U1.11 (G4), U4.21 (HVOUT6)
/G5: U1.15 (G5), U4.17 (HVOUT10)
/a: U1.14 (a), U4.18 (HVOUT9)
/b: U1.12 (b), U4.20 (HVOUT7)
/c: U1.7 (c), U4.25 (HVOUT2)
/d: U1.10 (d), U4.22 (HVOUT5)
/db: U1.9 (db), U4.23 (HVOUT4)
/dt: U1.3 (dt), U4.10 (HVOUT13)
/e: U1.5 (e), U4.12 (HVOUT11)
/f: U1.13 (f), U4.19 (HVOUT8)
/g: U1.4 (g), U4.11 (HVOUT12)
FILAMENT+: R6.1, U1.23 (F+)
FILAMENT-: R5.1, U1.17 (F-)
FIL_FWD: U2.7 (PB2), U5.4 (FWD)
FIL_REF: U2.4 (PA6), U5.6 (VREF)
FIL_REV: U2.6 (PB3), U5.5 (REV)
GND: C1.2, C3.2, C4.2, C5.2, C6.2, H1.1, H2.1, H3.1, H4.1, J1.1, J2.2, J3.1, J3.MP (MountPin), R2.1, R4.2, R14.2, U2.14 (GND), U3.2 (GND), U4.14 (GND), U5.8 (GND)
HV: C2.2, C3.1, D1.1 (K), R3.1, U4.1 (VPP_HV)
HV_BLANK: R14.1, U2.3 (PA5), U4.13 (BLANKING)
HV_CLOCK: U2.13 (PA3), U4.15 (CLOCK)
HV_DATA_IN: U2.11 (PA1), U4.27 (DATA_IN)
HV_DATA_OUT: U4.2 (DATA_OUT)
HV_EN: R1.2, U3.4 (EN)
HV_STROBE: U2.2 (PA4), U4.16 (STROBE)
unnamed: C2.1, R2.2, R3.2, U3.3 (FB)
unnamed: D1.2 (A), L1.2, U3.1 (SW)
unnamed: D2.1 (K), R4.1
unnamed: R5.2, U5.1 (OUT1)
unnamed: R6.2, U5.7 (OUT2)
unnamed: D2.2 (A), U2.5 (PA7)
unnamed: C4.1, L2.2, U5.2 (VM)
SCL: J1.4, J3.4, R7.2, U2.9 (PB0)
SDA: J1.3, J3.3, R8.1, U2.8 (PB1)
UPDI: J1.5, J2.1, U2.10 (~RESET/PA0)

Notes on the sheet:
High-Voltage Supply
Connector
Filament Drive
(alternatives: BD6211F-E2, BA6287F-E2)
Use X5R or X7R ceramic capacitors in high-voltage section
Mounting
Microcontroller
Vacuum Flourescent Display and Segment Driver

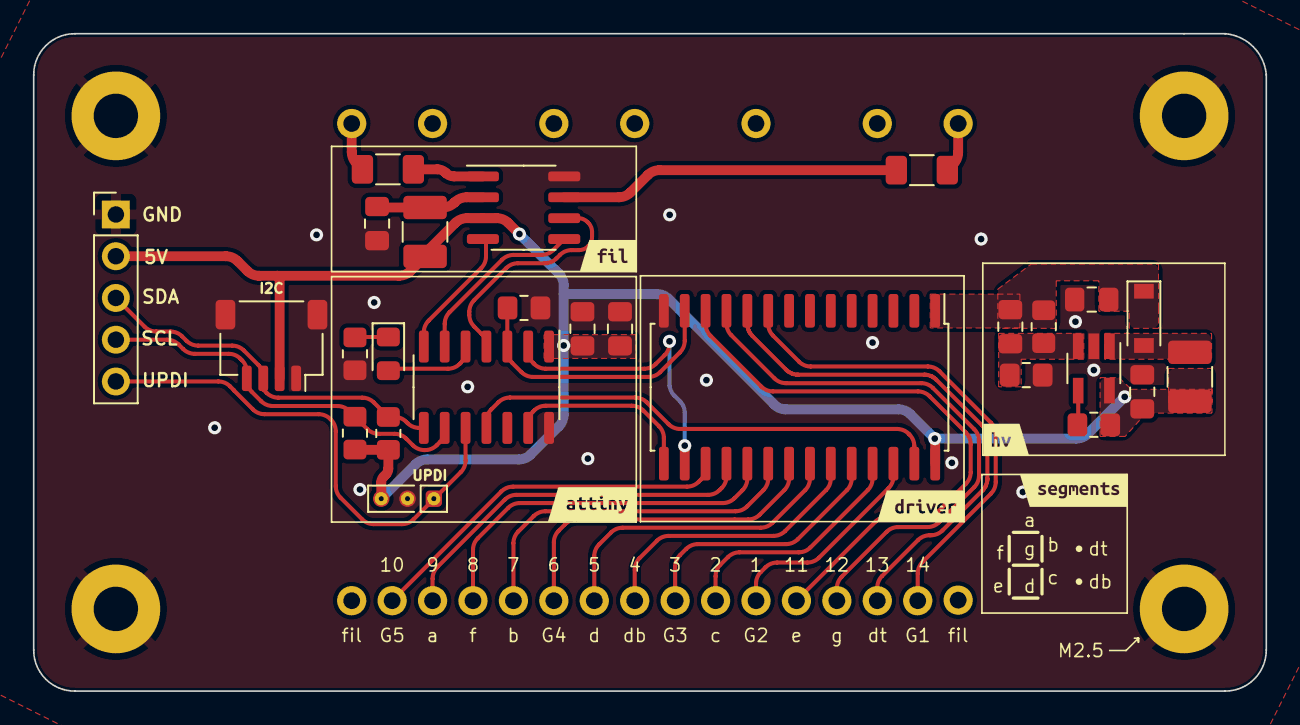
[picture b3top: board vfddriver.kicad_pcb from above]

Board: 2 copper layers, 75.0 x 40.0 mm, 37 parts (1 on the bottom side), 37 nets.

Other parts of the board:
kibuzzard-61E36C9E: G***; kibuzzard-61E36C9E
kibuzzard-61E36C30: G***; kibuzzard-61E36C30
kibuzzard-61E3696A: G***; kibuzzard-61E3696A
kibuzzard-61E3771A: G***; kibuzzard-61E3771A
kibuzzard-61E36996: G***; kibuzzard-61E36996
